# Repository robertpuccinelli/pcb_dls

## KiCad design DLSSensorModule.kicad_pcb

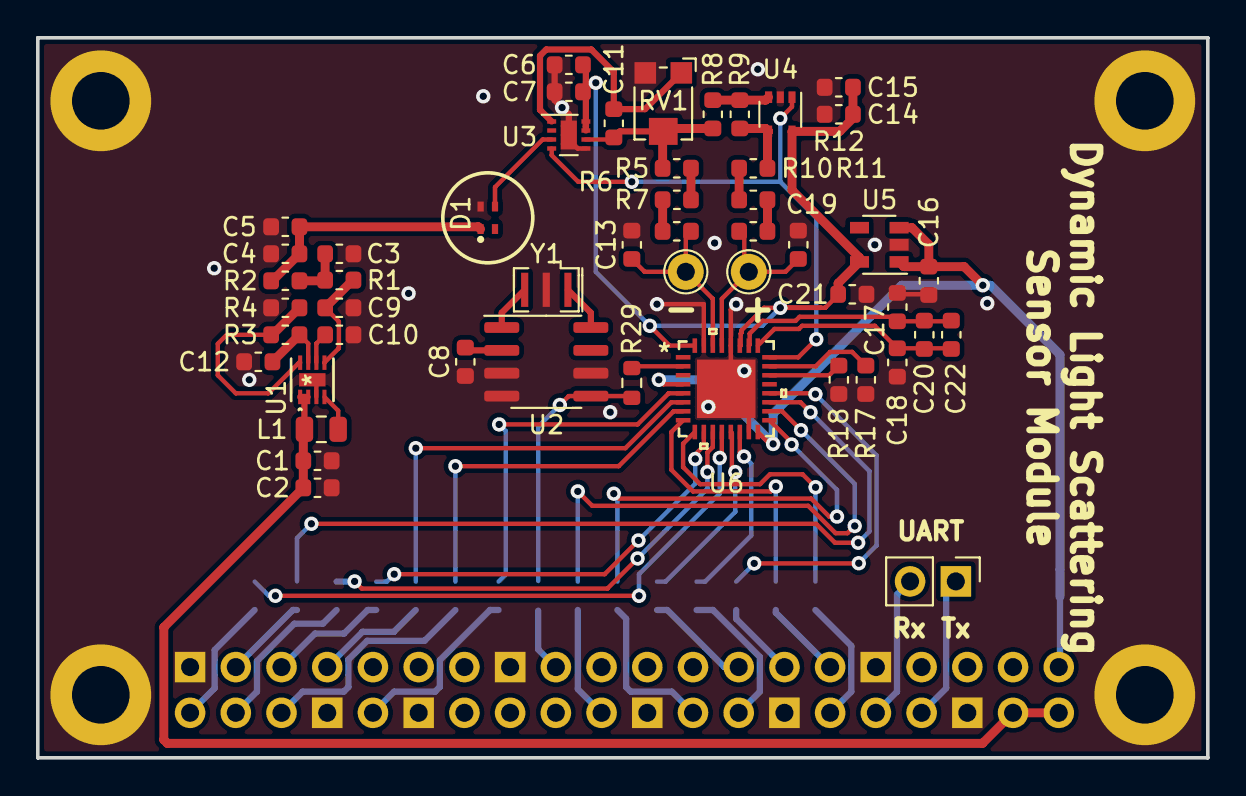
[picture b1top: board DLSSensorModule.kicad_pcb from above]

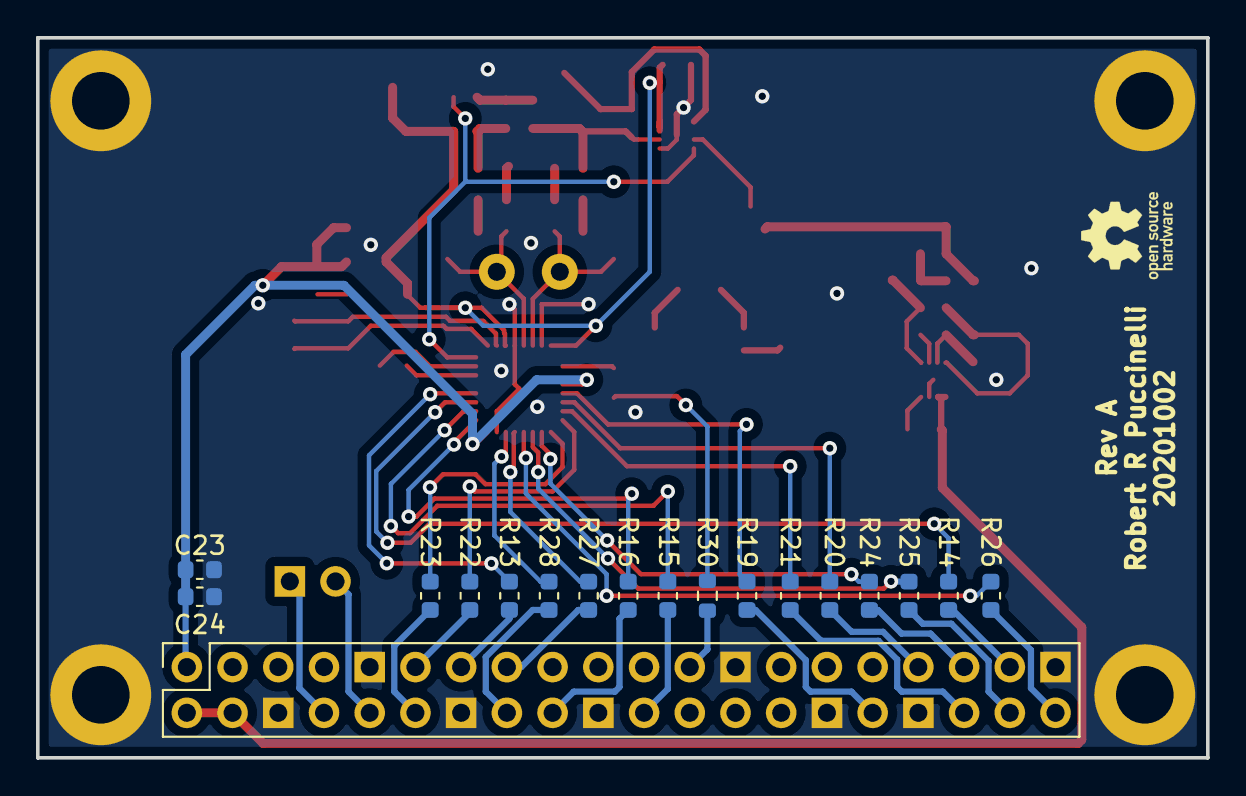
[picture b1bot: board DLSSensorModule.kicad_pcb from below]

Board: 4 copper layers, 65.0 x 40.0 mm, 73 parts (19 on the bottom side), 63 nets.

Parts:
C1, C2, C6, C14, C16, C21, C22, C24: 1uF; C_0603_1608Metric
C3, C8, C9, C10, C12, C17, C18, C20, C23: 100nF; C_0603_1608Metric
C4, C7, C15: 10nF; C_0603_1608Metric
C5, C13, C19: 100pF; C_0603_1608Metric
C11: 3pF; C_0603_1608Metric
D1: MICRORB-10020; CASE_512AK
H1, H2, H3, H4: Mount; MountingHole_3.2mm_M3_DIN965_Pad
J1: Pi Header; PinSocket_2x20_P2.54mm_Vertical
J2: UART; PinHeader_1x02_P2.54mm_Vertical
L1: 68uH; L_0805_2012Metric
LOGO1: Logo_Open_Hardware_Small; OSHW_logo
R1, R2, R5, R6, R7, R10, R11, R12: 50R; R_0603_1608Metric
R3: 110K; R_0603_1608Metric
R4: 887K; R_0603_1608Metric
R8, R9, R13, R14, R15, R16, R17, R18, R19, R20, R21, R22, R23, R24, R25, R26, R27, R28, R29, R30: 220R; R_0603_1608Metric
RV1: 10K; Potentiometer_Bourns_TC33X_Vertical
TP1, TP2: TestPoint; TestPoint_THTPad_D2.0mm_Drill1.0mm
U1: LT8410EDC-TRMPBF
U2: 501MLFT; SOIC-8_3.9x4.9mm_P1.27mm
U3: OPA855xDSG; WSON-8-1EP_2x2mm_P0.5mm_EP0.9x1.6mm
U4: MIC920; SOT-353_SC-70-5
U5: LP5907MFX-3.1; SOT-23-5
U6: AD9245BCPZ-65; AD9245BCPZ-80
Y1: 16MHz Resonator; Resonator_SMD_muRata_CSTxExxV-3Pin_3.0x1.1mm

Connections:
+3V3: C16.1, C23.2, C24.2, J1.1, U5.1, U5.3, U6.4, U6.16
+5V: C1.1, C2.1, J1.2, J1.4, L1.1, U1.1, U1.2
/BIAS: C9.1, R1.2, U1.5
/CLK: R29.1, R30.2, U2.5
/D0: J1.32, R19.1
/D1: J1.33, R20.1
/D2: J1.36, R21.1
/D3: J1.11, R22.1
/D4: J1.12, R23.1
/D5: J1.35, R24.1
/D6: J1.38, R25.1
/D7: J1.40, R26.1
/D8: J1.15, R27.1
/D9: J1.16, R28.1
/D10: J1.18, R16.1
/D11: J1.22, R15.1
/D12: J1.37, R14.1
/D13: J1.13, R13.1
/REFB: C18.2, C20.2, C22.2, U6.25
/REFT: C17.1, C20.1, C22.1, U6.26
/VIN+: C19.1, R12.2, TP2.1, U6.29
/VIN-: C13.1, R7.2, TP1.1, U6.30
/VREF: U3.4, U4.1, U6.24
GND: C1.2, C2.2, C3.2, C4.2, C5.2, C6.1, C7.2, C8.1, C9.2, C10.2, C12.2, C13.2, C14.1, C15.2, C16.2, C17.2, C18.1, C19.2, C21.2, C23.1, C24.1, D1.4, H1.1, H2.1, H3.1, H4.1, J1.6, J1.9, J1.14, J1.20, J1.25, J1.30, J1.34, J1.39, R4.1, R17.2, R18.2, RV1.3, U1.3, U1.9, U2.3, U2.4, U2.6, U3.5, U3.9, U4.2, U5.2, U6.15, U6.28, U6.31, U6.33, Y1.2
unnamed: C3.1, R1.1, R2.2
unnamed: C4.1, C5.1, D1.1, R2.1
unnamed: C10.1, U1.6
unnamed: C11.1, RV1.1, U3.1
unnamed: C11.2, R5.2, R8.1, RV1.2, U3.6
unnamed: C12.1, R3.1, U1.7
unnamed: D1.3, U3.3
unnamed: J1.8, J2.1
unnamed: J1.10, J2.2
unnamed: J1.23, R30.1
unnamed: L1.2, U1.4
unnamed: R3.2, R4.2, U1.8
unnamed: R5.1, R6.2
unnamed: R6.1, R7.1
unnamed: R8.2, R9.1, U4.3
unnamed: R10.1, R11.2
unnamed: R9.2, R10.2, U4.4
unnamed: R11.1, R12.1
unnamed: R13.2, U6.20
unnamed: R14.2, U6.19
unnamed: R15.2, U6.18
unnamed: R16.2, U6.17
unnamed: R17.1, U6.23
unnamed: R18.1, U6.22
unnamed: R19.2, U6.5
unnamed: R20.2, U6.6
unnamed: R21.2, U6.7
unnamed: R22.2, U6.8
unnamed: R23.2, U6.9
unnamed: R24.2, U6.10
unnamed: R25.2, U6.11
unnamed: R26.2, U6.12
unnamed: R27.2, U6.13
unnamed: R28.2, U6.14
unnamed: R29.2, U6.2
unnamed: U2.1, Y1.3
unnamed: U2.8, Y1.1
VDD: C8.2, U2.2
VDDA: C6.2, C7.1, C14.2, C15.1, C21.1, U3.7, U3.8, U4.5, U5.5, U6.27, U6.32

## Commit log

2023-07-14 move design to new repo

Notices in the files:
parts and their libraries:
Copyright 2016 Accelerated Designs. All rights reserved.
